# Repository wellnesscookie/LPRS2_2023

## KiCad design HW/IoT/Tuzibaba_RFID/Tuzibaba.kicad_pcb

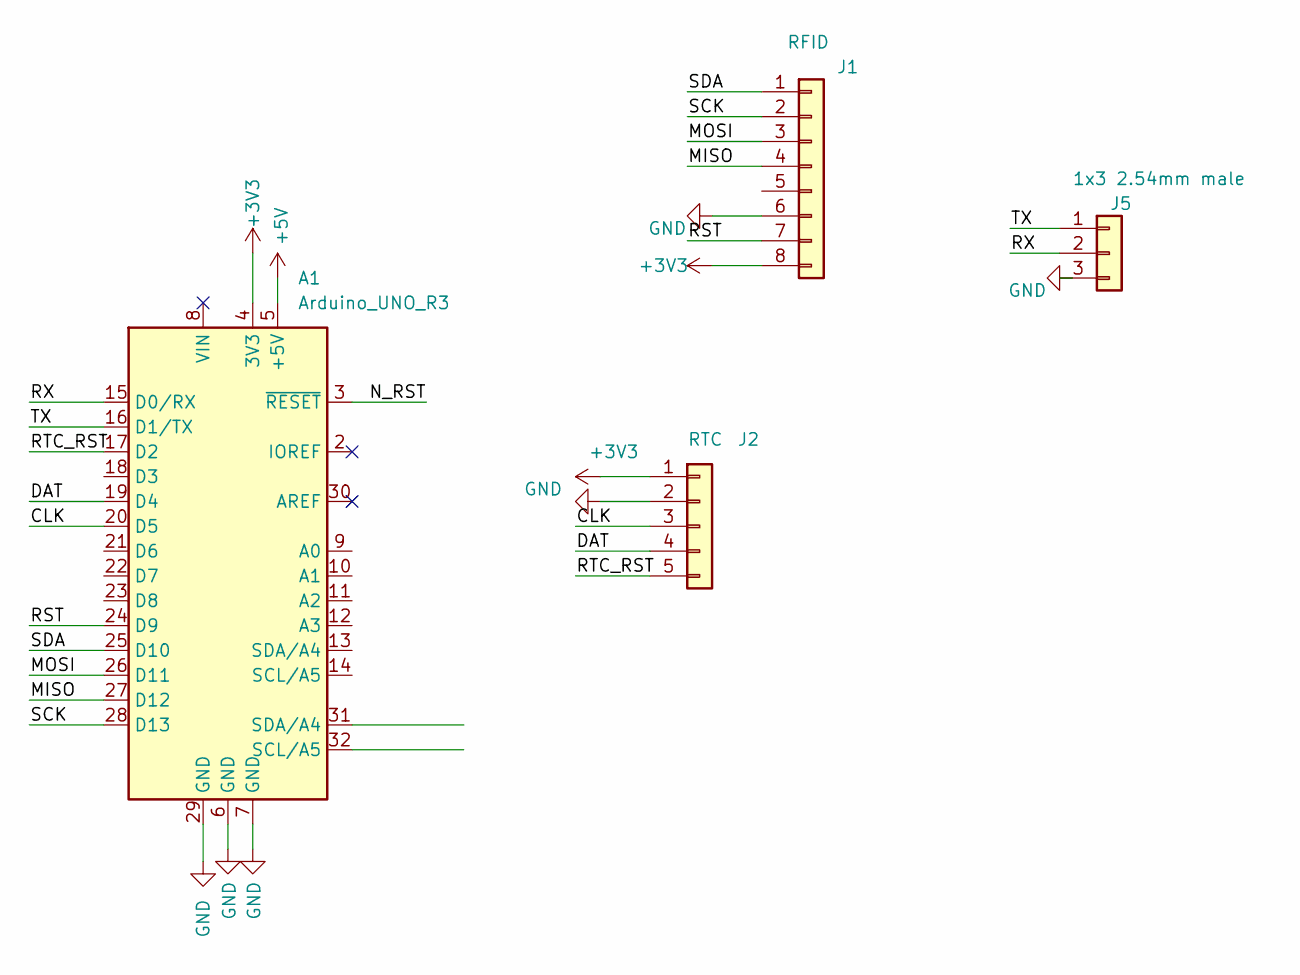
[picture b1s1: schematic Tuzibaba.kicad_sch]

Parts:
A1: Arduino_UNO_R3; Arduino_UNO_R3_WithMountingHoles_Snapped_to_P2.54mm
J1: RFID; PinSocket_1x08_P2.54mm_Vertical
J2: RTC; PinSocket_1x05_P2.54mm_Vertical
J5: 1x3 2.54mm male; PinSocket_1x03_P2.54mm_Vertical

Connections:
+3V3: A1.4 (3V3), J1.8, J2.1
+5V: A1.5 (+5V)
/CLK: A1.20 (D5), J2.3
/DAT: A1.19 (D4), J2.4
/MISO: A1.27 (D12), J1.4
/MOSI: A1.26 (D11), J1.3
/N_RST: A1.3 (~RESET)
/RST: A1.24 (D9), J1.7
/RTC_RST: A1.17 (D2), J2.5
/RX: A1.15 (D0/RX), J5.2
/SCK: A1.28 (D13), J1.2
/SDA: A1.25 (D10), J1.1
/TX: A1.16 (D1/TX), J5.1
GND: A1.6 (GND), A1.7 (GND), A1.29 (GND), J1.6, J2.2, J5.3

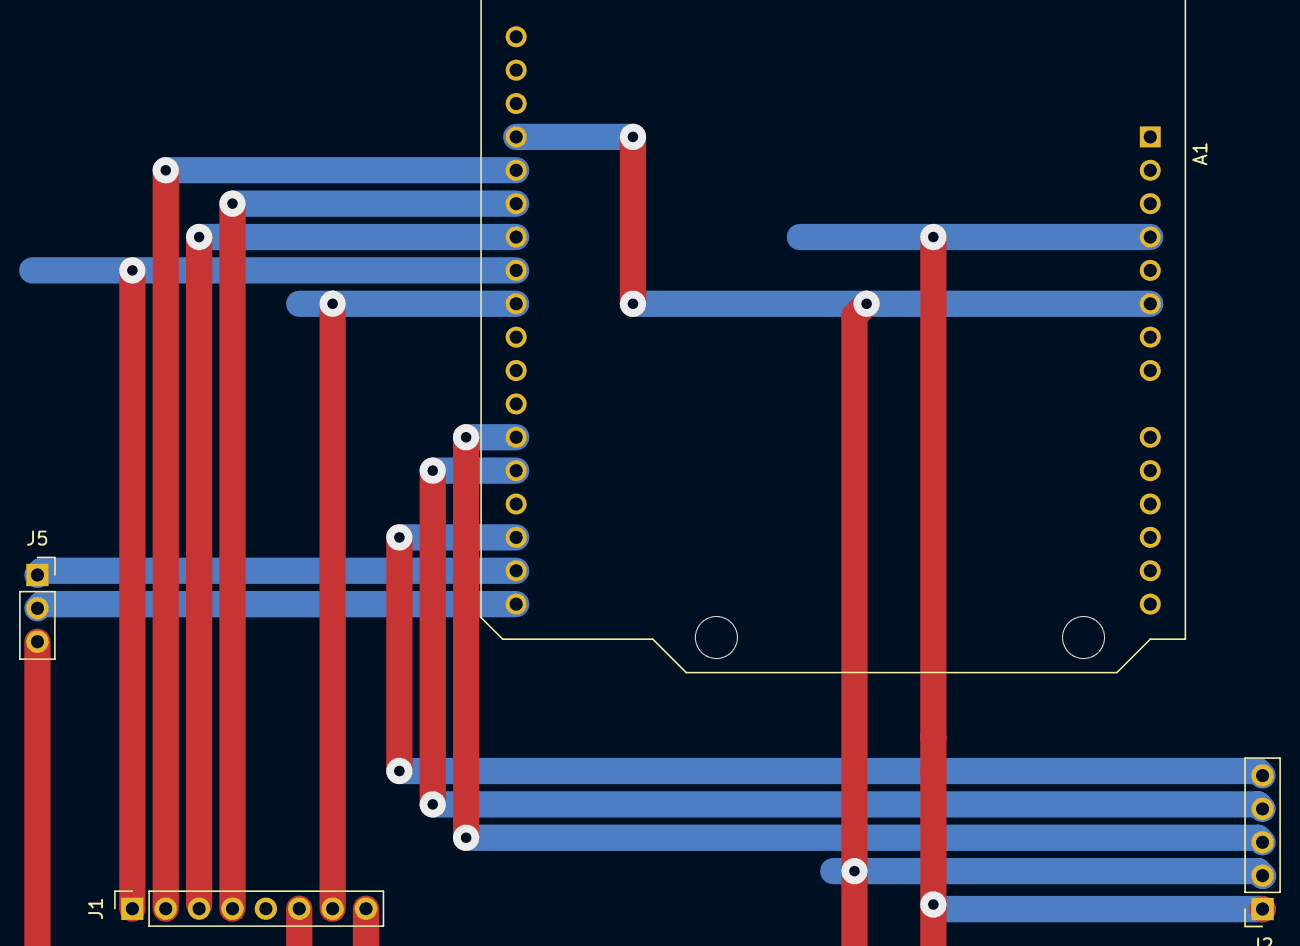
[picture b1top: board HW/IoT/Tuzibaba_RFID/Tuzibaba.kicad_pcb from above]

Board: 2 copper layers, 4 parts (0 on the bottom side), 12 nets.

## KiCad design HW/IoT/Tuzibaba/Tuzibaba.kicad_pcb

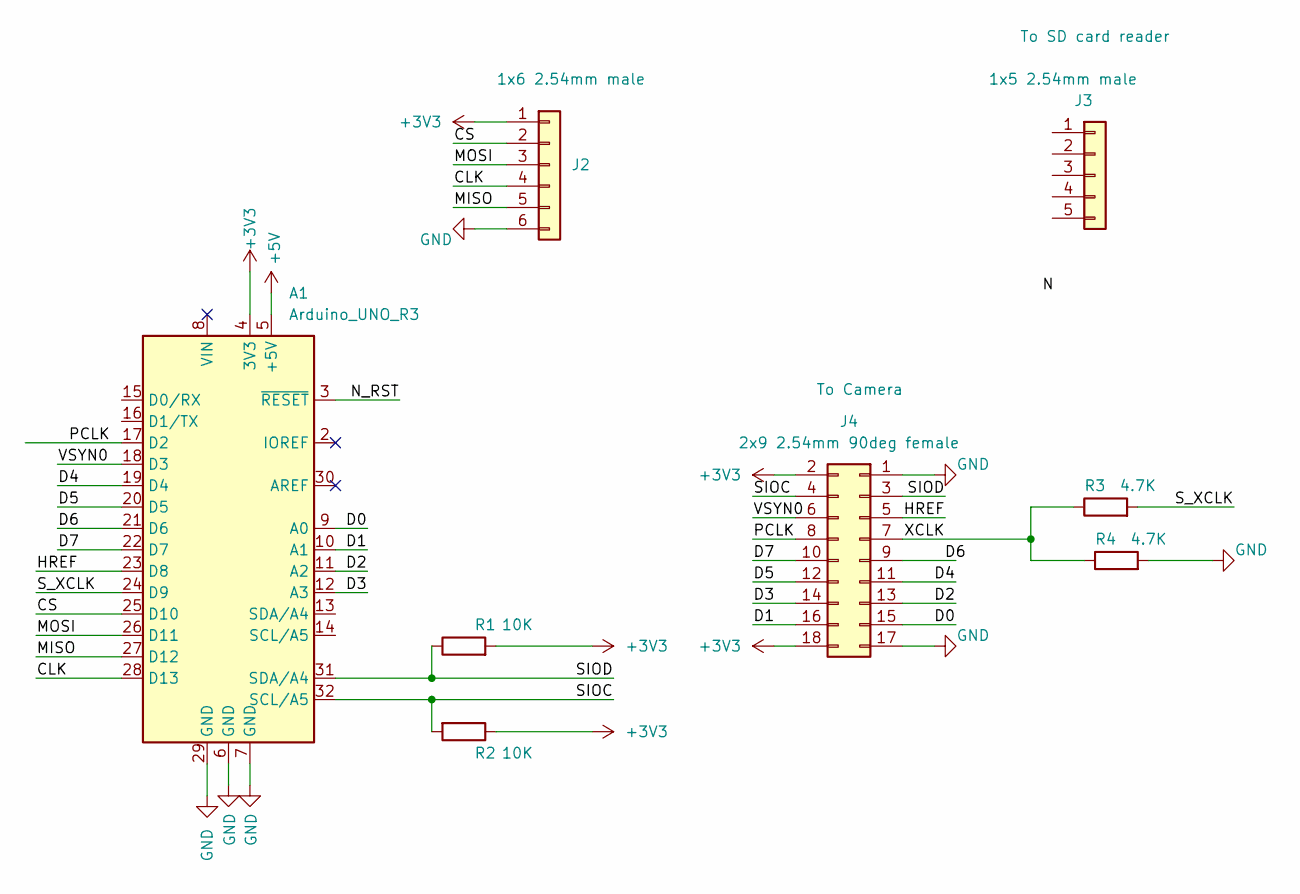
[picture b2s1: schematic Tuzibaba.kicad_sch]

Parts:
A1: Arduino_UNO_R3; Arduino_UNO_R3_WithMountingHoles_Snapped_to_P2.54mm
J2: 1x6 2.54mm male; PinSocket_1x06_P2.54mm_Vertical
J3: 1x5 2.54mm male; PinSocket_1x05_P2.54mm_Vertical
J4: 2x9 2.54mm 90deg female; PinSocket_2x09_P2.54mm_Vertical
R1, R2: 10K; R_Axial_DIN0207_L6.3mm_D2.5mm_P7.62mm_Horizontal
R3, R4: 4.7K; R_Axial_DIN0207_L6.3mm_D2.5mm_P7.62mm_Horizontal

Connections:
+3V3: A1.4 (3V3), J2.1, J4.2, J4.18, R1.2, R2.1
+5V: A1.5 (+5V)
/CLK: A1.28 (D13), J2.4
/CS: A1.25 (D10), J2.2
/D0: A1.9 (A0), J4.15
/D1: A1.10 (A1), J4.16
/D2: A1.11 (A2), J4.13
/D3: A1.12 (A3), J4.14
/D4: A1.19 (D4), J4.11
/D5: A1.20 (D5), J4.12
/D6: A1.21 (D6)
/D7: A1.22 (D7), J4.10
/HREF: A1.23 (D8), J4.5
/MISO: A1.27 (D12), J2.5
/MOSI: A1.26 (D11), J2.3
/N_RST: A1.3 (~RESET)
/PCLK: A1.17 (D2), J4.8
/SIOC: A1.32 (SCL/A5), J4.4, R2.2
/SIOD: A1.31 (SDA/A4), J4.3, R1.1
/S_XCLK: A1.24 (D9), R3.2
/VSYN0: A1.18 (D3), J4.6
/XCLK: J4.7, R3.1, R4.1
GND: A1.6 (GND), A1.7 (GND), A1.29 (GND), J2.6, J4.1, J4.17, R4.2

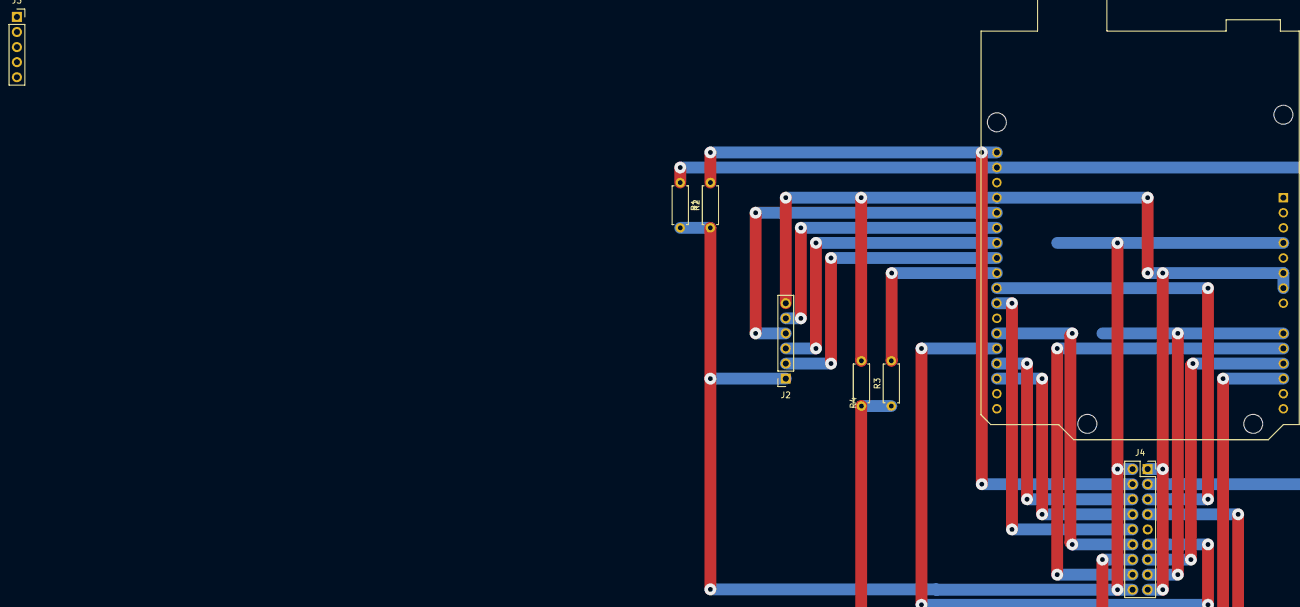
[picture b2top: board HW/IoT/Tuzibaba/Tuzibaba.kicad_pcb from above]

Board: 2 copper layers, 8 parts (0 on the bottom side), 20 nets.

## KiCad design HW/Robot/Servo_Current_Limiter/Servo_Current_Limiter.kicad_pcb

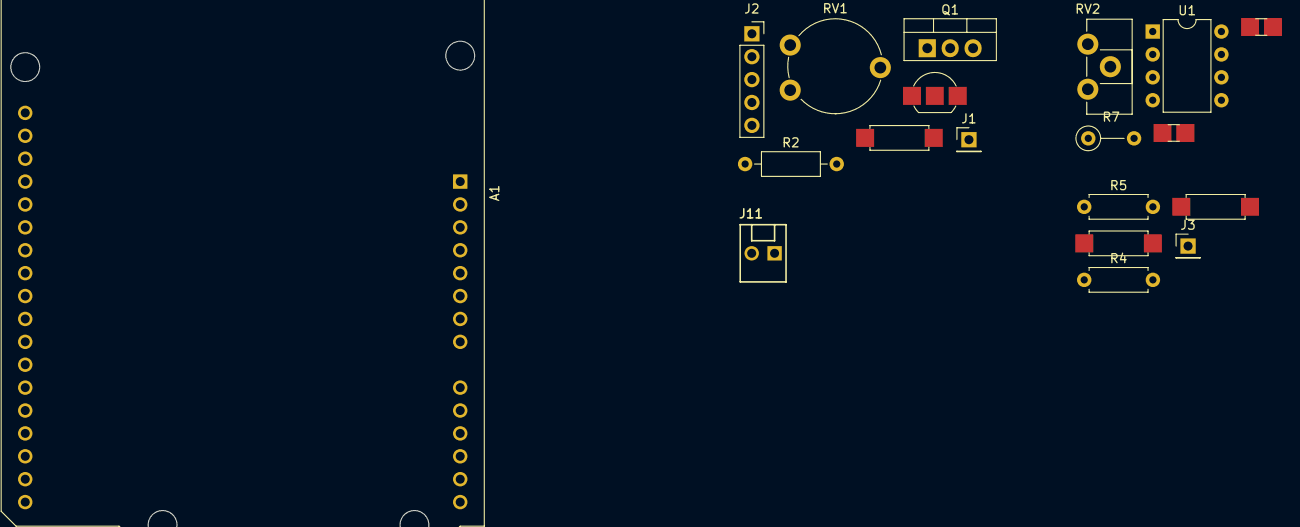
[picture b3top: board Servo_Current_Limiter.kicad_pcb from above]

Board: 2 copper layers, 19 parts (0 on the bottom side), 14 nets, no tracks yet.

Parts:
A1: Arduino_UNO_R3; Arduino_UNO_R3_WithMountingHoles_Snapped_to_P2.54mm
C1, C2: 100n; C_Disc_D3.0mm_W1.6mm_Pinf
J1, J3: 1x1 2.54mm male; PinHeader_1x01_P2.54mm_Vertical
J2: 1x5 2.54mm male; PinSocket_1x05_P2.54mm_Vertical
J11: 1x2 2.54mm male; MOLEX-22-23-2021
Q1: IRF4905; TO-220-3_Vertical
Q2: BC338; TO-92_Inline_inf
R1: 220; R_Axial_DIN0207_L6.3mm_D2.5mm_Pinf_Horizontal
R2: 0.1; R_Axial_DIN0207_L6.3mm_D2.5mm_P10.16mm_Horizontal
R3, R6: 220k; R_Axial_DIN0207_L6.3mm_D2.5mm_Pinf_Horizontal
R4, R5: 220k; R_Axial_DIN0207_L6.3mm_D2.5mm_P7.62mm_Horizontal
R7: 1k5; R_Axial_DIN0207_L6.3mm_D2.5mm_P5.08mm_Vertical
RV1: 250; Potentiometer_Piher_PT-10-V10_Vertical
RV2: 100k; Potentiometer_Piher_PT-10-H01_Horizontal
U1: TL071; DIP-8_W7.62mm

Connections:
+5V: A1.5 (+5V), C1.1, J11.1, Q1.3 (S), R1.1, U1.7 (V+)
/DIS0: A1.17 (D2), Q1.1 (G), Q2.1 (C)
/OUT0: A1.9 (A0), J3.1, Q2.2 (B), R6.1, U1.6
/ch0/N: J2.4, R2.1, R4.1
/ch0/P: Q1.2 (D), R2.2, R5.2
/ch0/sub/op/IN+: R3.2, R4.2, U1.3 (+)
/ch0/sub/op/IN-: R5.1, R6.2, U1.2 (-)
GND: A1.6 (GND), A1.7 (GND), C2.1, J2.5, J11.2, R7.2, RV1.3, U1.4 (V-)
GNDA: C1.2, C2.2, R3.1
unnamed: J1.1, Q2.3 (E), RV1.2
unnamed: R1.2, RV1.1
unnamed: R7.1, RV2.2
unnamed: RV2.1, U1.5 (NULL)
unnamed: RV2.3, U1.1 (NULL)

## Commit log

2023-05-16 Adding resources.
2023-05-18 File for notes.
2023-05-18 Adding.
2023-05-18 Small change.
2023-05-18 HW started.
2023-05-18 Regrouping.
2023-05-18 Finished one circuit.
2023-05-18 Now finished.
2023-05-19 add SD card example information
2023-05-19 add OV7670 camera example URL
2023-05-19 Add RC522 RFID example URL
2023-05-19 Update requirements for Arduino camera module
2023-05-19 Started sch.
2023-05-20 Adding useful links
2023-05-20 Add changes made to schem and pcb
2023-05-22 Update and rename getRFID.ino to GetCardIDandTime
    added time to RFID reader
2023-05-22 Finalizing schematic
2023-05-23 Initial code for OV7670 module
2023-05-23 Update with some useful links
2023-05-23 Update with useful links
2023-05-23 Update GetCardIDandTime
    added communication with another arduino
2023-05-23 Update schematic and pcb
2023-05-24 Update GetCardIDandTime
    sync time and addapt for sd card
2023-05-24 Recode ov7670 lib to use XCLK from pin9
2023-05-24 uart_sd_card.ino
    uart + sd_card optimization
2023-06-06 Update schematic and pcb for camera
    FOR IT IS FINALLY WORKING
2023-06-13 Finalizing code for Arduino with camera
2023-06-13 Increasing baud rate and finalizing code
2023-06-13 Finalize schematic and pcb for arduino with camera
2023-06-13 Add 3pin connector for UART w/ 2nd arduino
2023-06-15 Clear repository of irrelevant directories and files
2023-06-15 Add python script and rearange folders
